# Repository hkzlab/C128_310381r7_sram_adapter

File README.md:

# C128 310381 R7 SRAM Adapter

## DISCLAIMER

Any use of this project is **under your own responsibility**.
You will be responsible of checking the correct construction and functionality of your board.
By using this project You will agree that I cannot be held responsible if it will destroy any of your devices, damage your computer, burn down your house or whatever.

**WARNING**: This device was only tested to fit on a motherboard model 310381R7!!!

**ANOTHER WARNING**: This device is still under testing, and while it seems to be working without issues on my C128, there are no guarantees!

## Introduction

This board implements a static RAM replacement for the DRAMs on a C128 with a 310381R7 motherboard.

You will have to remove and socket your DRAM ICs to install this board. Please, do not kill innocent DRAM ICs by cutting their legs!

### Ordering the boards

You can order the board for this project at [PCBWay](https://www.pcbway.com/project/shareproject/Commodore_C128_310381_R7_SRAM_Adapter_aeccc292.html) and support me or download 
the gerbers and have them printed wherever you like!!!

## Features

- You can choose to use SMD or DIP components
- Once the DRAMs are socketed, the board is easy to plug in and remove

## Hardware

The board was designed with [KiCad](https://kicad.org/) EDA.

### Bill of Materials

| Component              | Qty | Type / Value                                            | Notes                                                                |
| ---------------------- | --- | ------------------------------------------------------- | -------------------------------------------------------------------- |
| C1, C2, C3             |  3  | 100nF ceramic cap, SMD 1206 or 2.54mm through hole      | Decoupling caps, rated at least 10V.                                 |
| C5, C6                 |  2  | ~82-820pF ceramic cap, 1206 or THT 2.54mm               | Optional tweak on CAS timing, normally no need to fit this           |
| U1, U4                 |  1  | 128Kx8 SRAM, DIP32 or SOP32      | I tested 85ns SRAMs without issue. 628128 pinout. Install either U1 or U4.                  |
| U2                     |  1  | 74HCT00, DIP14 or SO14           | Can be replaced with an ACT/ALS/LS/F. Do NOT use an HC. Note: F/LS/ACT/HCT currently tested |
| U3                     |  1  | 74HCT573, DIP 20 or TSSOP20      | Can be replaced with an ACT/ALS/LS/F. Do NOT use an HC. Note: Only HCT currently tested     |
| J2                     |  1  | Angled header or wire            | Install an angled header or a wire that goes to the second CAS line, U38 pin 15             |
| Headers                |  1  | 40p 2.54mm machined header strip | Cut it into 4x8p and 6x1p pieces, then solder on the underside                              |

### Known Issues

I could not detect stability issues. Yet.

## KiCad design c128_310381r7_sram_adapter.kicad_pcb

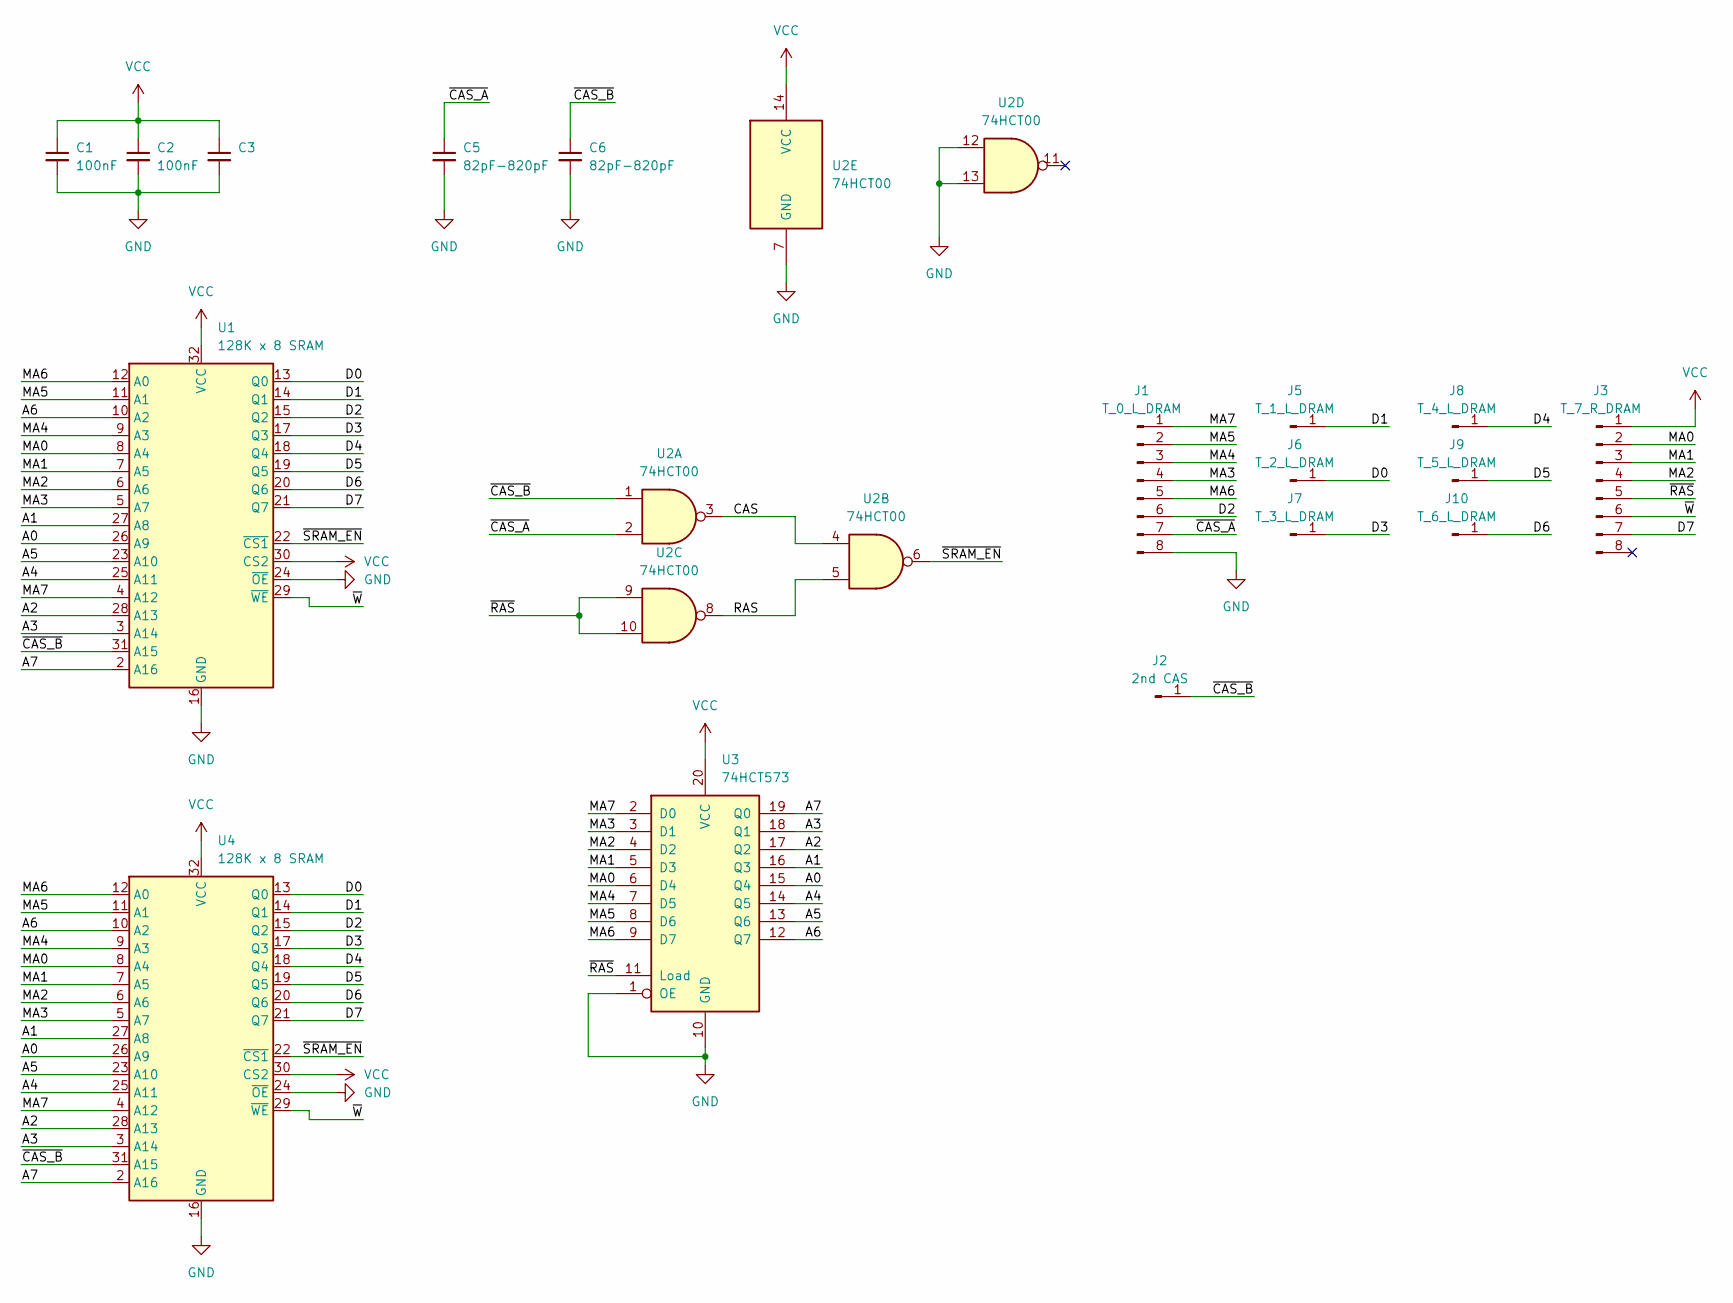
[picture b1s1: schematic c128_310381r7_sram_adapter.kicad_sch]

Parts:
C1, C2, C3: 100nF; C_Disc_1206_P5.00mm
C5, C6: 82pF-820pF; C_Disc_1206_P2.50mm
J1: T_0_L_DRAM; PinHeader_1x08_P2.54mm_Vertical
J2: 2nd CAS; PinHeader_1x01_P2.54mm_Horizontal
J3: T_7_R_DRAM; PinHeader_1x08_P2.54mm_Vertical
J5: T_1_L_DRAM; PinHeader_1x01_P2.54mm_Vertical
J6: T_2_L_DRAM; PinHeader_1x01_P2.54mm_Vertical
J7: T_3_L_DRAM; PinHeader_1x01_P2.54mm_Vertical
J8: T_4_L_DRAM; PinHeader_1x01_P2.54mm_Vertical
J9: T_5_L_DRAM; PinHeader_1x01_P2.54mm_Vertical
J10: T_6_L_DRAM; PinHeader_1x01_P2.54mm_Vertical
U1: 128K x 8 SRAM; DIP-32_W15.24mm
U2: 74HCT00; DIP-SO-14
U3: 74HCT573; DIP-TSSOP-20
U4: 128K x 8 SRAM; SOP-32_11.305x20.495mm_P1.27mm

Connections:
/A0: U1.26 (A9), U3.15 (Q4), U4.26 (A9)
/A1: U1.27 (A8), U3.16 (Q3), U4.27 (A8)
/A2: U1.28 (A13), U3.17 (Q2), U4.28 (A13)
/A3: U1.3 (A14), U3.18 (Q1), U4.3 (A14)
/A4: U1.25 (A11), U3.14 (Q5), U4.25 (A11)
/A5: U1.23 (A10), U3.13 (Q6), U4.23 (A10)
/A6: U1.10 (A2), U3.12 (Q7), U4.10 (A2)
/A7: U1.2 (A16), U3.19 (Q0), U4.2 (A16)
/CAS: U2.3, U2.4
/D0: J6.1, U1.13 (Q0), U4.13 (Q0)
/D1: J5.1, U1.14 (Q1), U4.14 (Q1)
/D2: J1.6, U1.15 (Q2), U4.15 (Q2)
/D3: J7.1, U1.17 (Q3), U4.17 (Q3)
/D4: J8.1, U1.18 (Q4), U4.18 (Q4)
/D5: J9.1, U1.19 (Q5), U4.19 (Q5)
/D6: J10.1, U1.20 (Q6), U4.20 (Q6)
/D7: J3.7, U1.21 (Q7), U4.21 (Q7)
/MA0: J3.2, U1.8 (A4), U3.6 (D4), U4.8 (A4)
/MA1: J3.3, U1.7 (A5), U3.5 (D3), U4.7 (A5)
/MA2: J3.4, U1.6 (A6), U3.4 (D2), U4.6 (A6)
/MA3: J1.4, U1.5 (A7), U3.3 (D1), U4.5 (A7)
/MA4: J1.3, U1.9 (A3), U3.7 (D5), U4.9 (A3)
/MA5: J1.2, U1.11 (A1), U3.8 (D6), U4.11 (A1)
/MA6: J1.5, U1.12 (A0), U3.9 (D7), U4.12 (A0)
/MA7: J1.1, U1.4 (A12), U3.2 (D0), U4.4 (A12)
/RAS: U2.5, U2.8
/~CAS_A: C5.1, J1.7, U2.2
/~CAS_B: C6.1, J2.1, U1.31 (A15), U2.1, U4.31 (A15)
/~RAS: J3.5, U2.9, U2.10, U3.11 (Load)
/~SRAM_EN: U1.22 (~CS1), U2.6, U4.22 (~CS1)
/~W: J3.6, U1.29 (~WE), U4.29 (~WE)
GND: C1.2, C2.2, C3.2, C5.2, C6.2, J1.8, U1.16 (GND), U1.24 (~OE), U2.7 (GND), U2.12, U2.13, U3.1 (OE), U3.10 (GND), U4.16 (GND), U4.24 (~OE)
VCC: C1.1, C2.1, C3.1, J3.1, U1.30 (CS2), U1.32 (VCC), U2.14 (VCC), U3.20 (VCC), U4.30 (CS2), U4.32 (VCC)

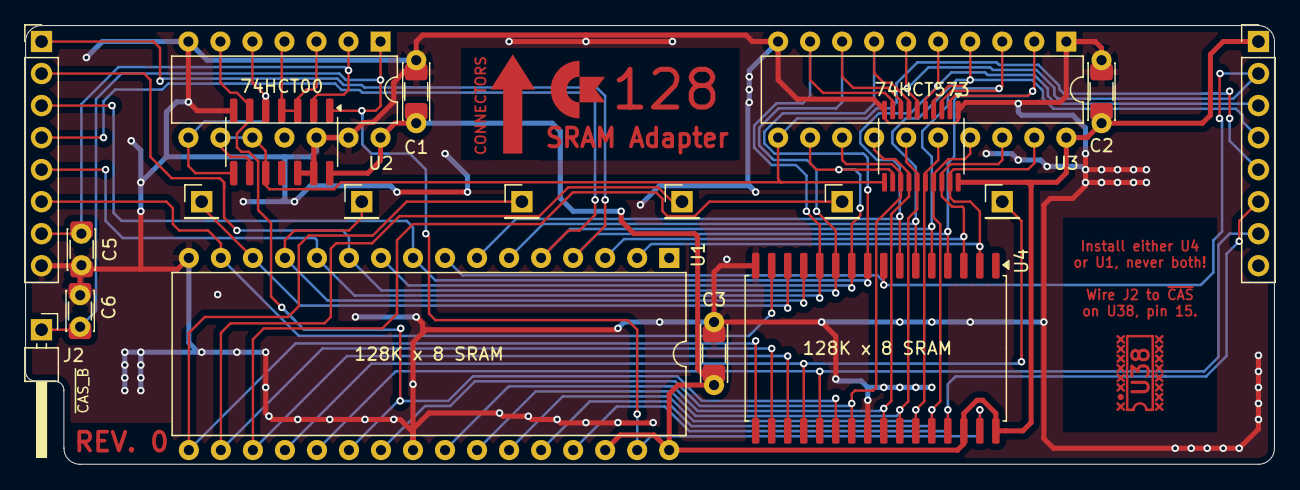
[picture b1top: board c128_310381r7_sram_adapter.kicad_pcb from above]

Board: 2 copper layers, 99.1 x 34.8 mm, 18 parts (0 on the bottom side), 33 nets.

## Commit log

2025-02-08 Initial schematic for the SRAM adapter
2025-02-08 Schematic for the connections of the SRAM adapter
2025-02-09 Wire A15 to /CAS_A signal
2025-02-09 Add custom footprints for components in this adapter
2025-02-09 Begin drawing traces
2025-02-09 Complete routing of first revision of the adapter
2025-02-10 Update silkscreen and drawings on the PCB
2025-03-02 Add rev_0 gerbers
2025-03-23 Update the README
2025-03-23 Add additional warnings
2025-03-23 Update README to include link to PCBway project page
2025-03-26 Update the README with types of tested ICs
2025-03-26 Update project files with new kicad version
